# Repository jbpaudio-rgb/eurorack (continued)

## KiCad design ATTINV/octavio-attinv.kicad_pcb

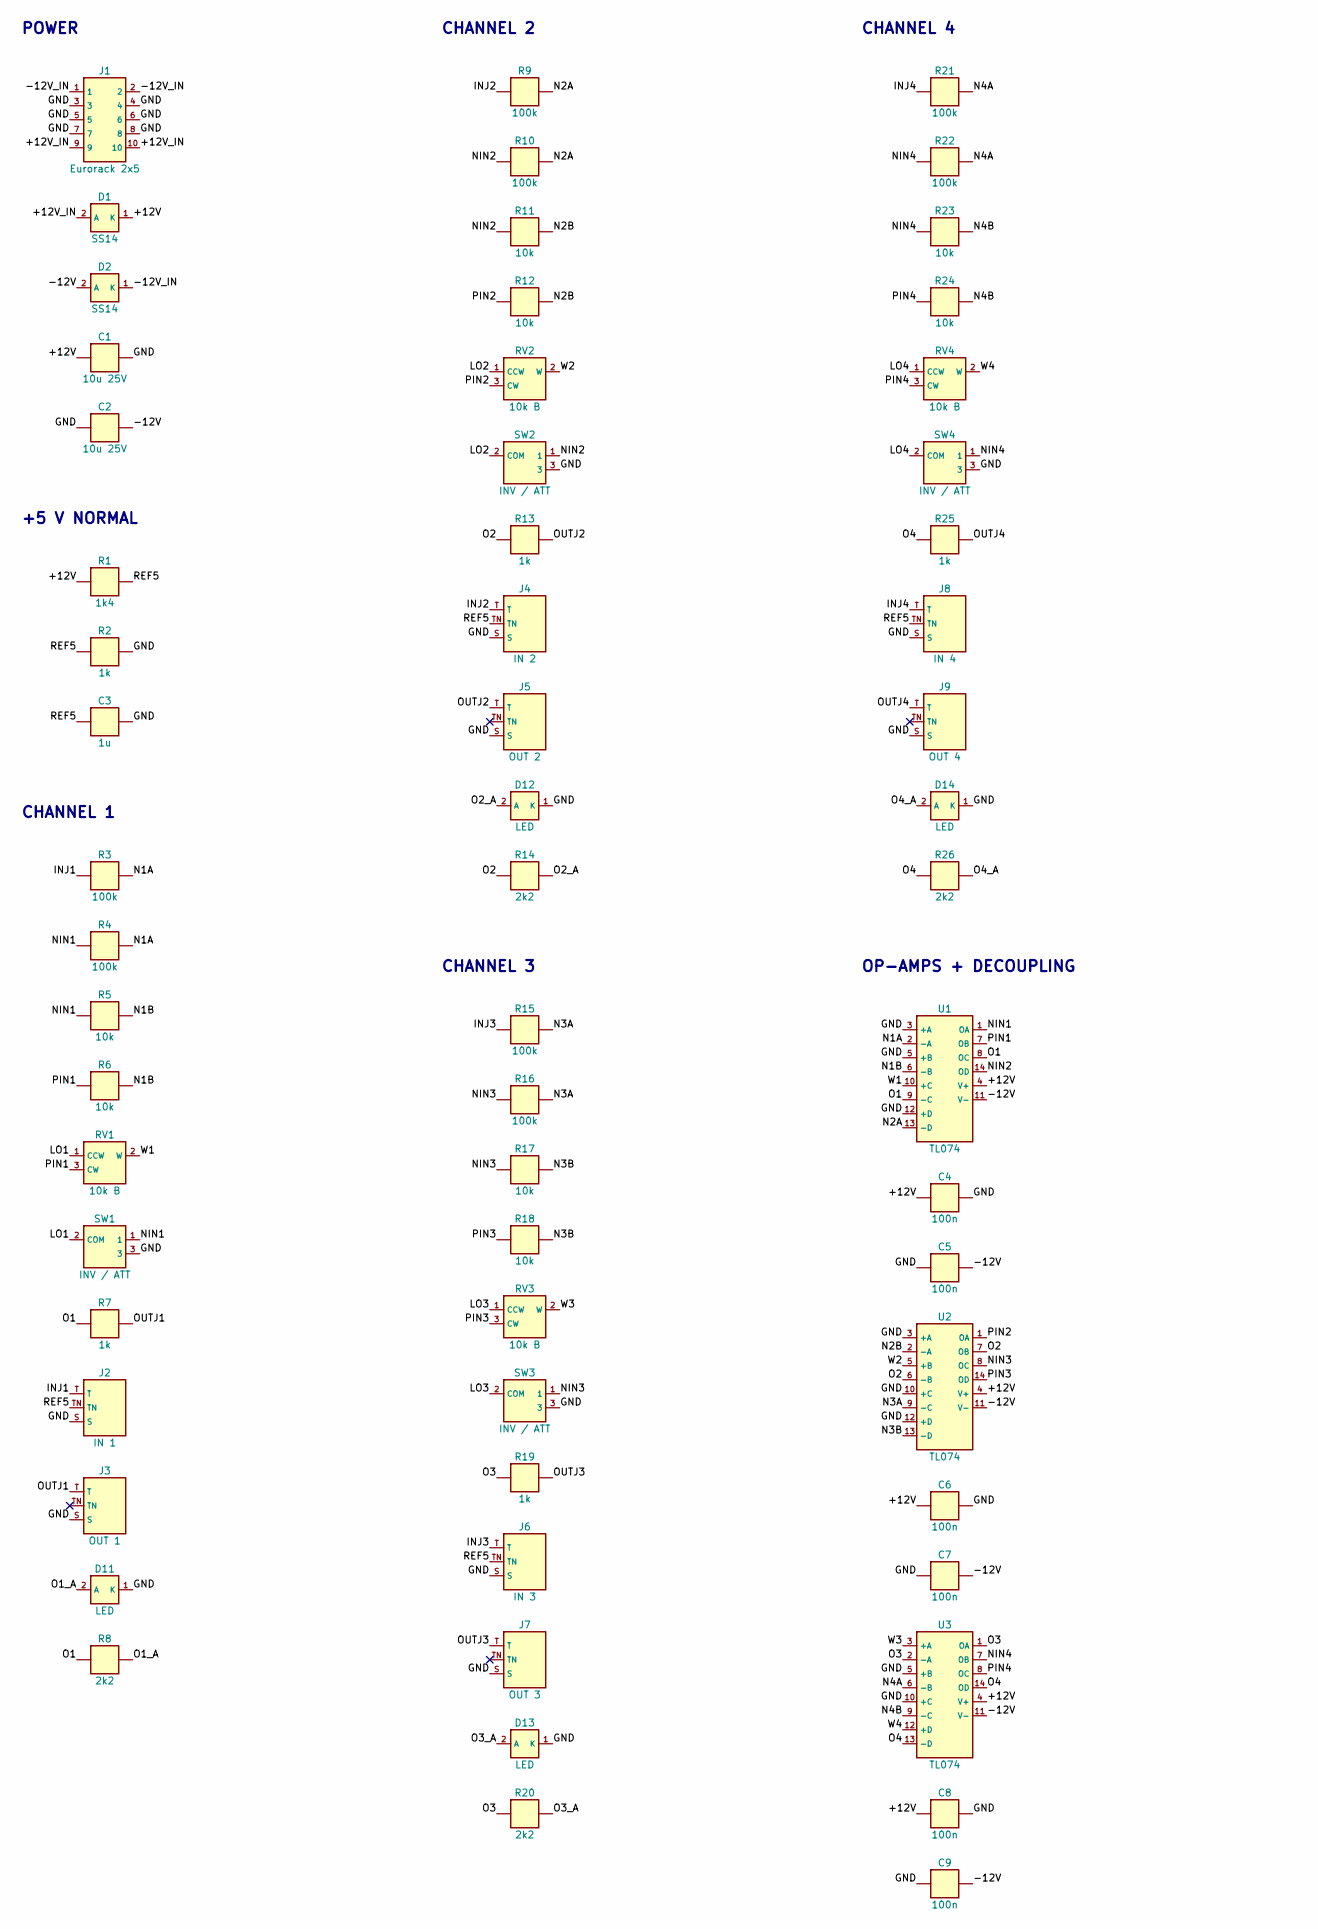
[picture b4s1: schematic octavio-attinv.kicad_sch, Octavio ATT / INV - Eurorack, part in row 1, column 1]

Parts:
C1, C2: 10u 25V; C_1206_3216Metric; MPN X5R/X7R 1206
C3: 1u; C_0603_1608Metric; MPN X7R 0603 25 V
C4, C5, C6, C7, C8, C9: 100n; C_0603_1608Metric
D1, D2: SS14; D_SMA; MPN SS14 (40 V 1 A Schottky)
D11, D12, D13, D14: LED; LED_D3.0mm; MPN LED 3 mm bicolore 2 pattes rouge / vert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
J1: Eurorack 2x5; IDC-Header_2x05_P2.54mm_Vertical; MPN Shrouded header 2x5 2.54 mm
J2: IN 1; Jack_3.5mm_Thonkiconn_PJ398SM; MPN QingPu WQP-PJ301M-12 (Thonkiconn)
J3: OUT 1; Jack_3.5mm_Thonkiconn_PJ398SM; MPN QingPu WQP-PJ301M-12 (Thonkiconn)
J4: IN 2; Jack_3.5mm_Thonkiconn_PJ398SM; MPN QingPu WQP-PJ301M-12 (Thonkiconn)
J5: OUT 2; Jack_3.5mm_Thonkiconn_PJ398SM; MPN QingPu WQP-PJ301M-12 (Thonkiconn)
J6: IN 3; Jack_3.5mm_Thonkiconn_PJ398SM; MPN QingPu WQP-PJ301M-12 (Thonkiconn)
J7: OUT 3; Jack_3.5mm_Thonkiconn_PJ398SM; MPN QingPu WQP-PJ301M-12 (Thonkiconn)
J8: IN 4; Jack_3.5mm_Thonkiconn_PJ398SM; MPN QingPu WQP-PJ301M-12 (Thonkiconn)
J9: OUT 4; Jack_3.5mm_Thonkiconn_PJ398SM; MPN QingPu WQP-PJ301M-12 (Thonkiconn)
R1: 1k4; R_0603_1608Metric
R2, R7, R13, R19, R25: 1k; R_0603_1608Metric
R3, R4, R9, R10, R15, R16, R21, R22: 100k; R_0603_1608Metric
R5, R6, R11, R12, R17, R18, R23, R24: 10k; R_0603_1608Metric
R8, R14, R20, R26: 2k2; R_0603_1608Metric
RV1, RV2, RV3, RV4: 10k B; Pot_Alpha_9mm_Vertical; MPN POT-R09V-10K B (9 mm vertical)
SW1, SW2, SW3, SW4: INV / ATT; Toggle_SPDT_Dailywell_2MS1; MPN Dailywell 2MS1T1B1M2QES (SPDT ON-ON) : 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
U1, U2, U3: TL074; SOIC-14_3.9x8.7mm_P1.27mm; MPN TL074CDR

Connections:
+12V: C1.1, C4.1, C6.1, C8.1, D1.1 (K), R1.1, U1.4 (V+), U2.4 (V+), U3.4 (V+)
+12V_IN: D1.2 (A), J1.9, J1.10
-12V: C2.2, C5.2, C7.2, C9.2, D2.2 (A), U1.11 (V-), U2.11 (V-), U3.11 (V-)
-12V_IN: D2.1 (K), J1.1, J1.2
GND: C1.2, C2.1, C3.2, C4.2, C5.1, C6.2, C7.1, C8.2, C9.1, D11.1 (K), D12.1 (K), D13.1 (K), D14.1 (K), J1.3, J1.4, J1.5, J1.6, J1.7, J1.8, J2.S, J3.S, J4.S, J5.S, J6.S, J7.S, J8.S, J9.S, R2.2, SW1.3, SW2.3, SW3.3, SW4.3, U1.3 (+A), U1.5 (+B), U1.12 (+D), U2.3 (+A), U2.10 (+C), U2.12 (+D), U3.5 (+B), U3.10 (+C)
INJ1: J2.T, R3.1
INJ2: J4.T, R9.1
INJ3: J6.T, R15.1
INJ4: J8.T, R21.1
LO1: RV1.1 (CCW), SW1.2 (COM)
LO2: RV2.1 (CCW), SW2.2 (COM)
LO3: RV3.1 (CCW), SW3.2 (COM)
LO4: RV4.1 (CCW), SW4.2 (COM)
N1A: R3.2, R4.2, U1.2 (-A)
N1B: R5.2, R6.2, U1.6 (-B)
N2A: R9.2, R10.2, U1.13 (-D)
N2B: R11.2, R12.2, U2.2 (-A)
N3A: R15.2, R16.2, U2.9 (-C)
N3B: R17.2, R18.2, U2.13 (-D)
N4A: R21.2, R22.2, U3.6 (-B)
N4B: R23.2, R24.2, U3.9 (-C)
NIN1: R4.1, R5.1, SW1.1, U1.1 (OA)
NIN2: R10.1, R11.1, SW2.1, U1.14 (OD)
NIN3: R16.1, R17.1, SW3.1, U2.8 (OC)
NIN4: R22.1, R23.1, SW4.1, U3.7 (OB)
O1: R7.1, R8.1, U1.8 (OC), U1.9 (-C)
O1_A: D11.2 (A), R8.2
O2: R13.1, R14.1, U2.6 (-B), U2.7 (OB)
O2_A: D12.2 (A), R14.2
O3: R19.1, R20.1, U3.1 (OA), U3.2 (-A)
O3_A: D13.2 (A), R20.2
O4: R25.1, R26.1, U3.13 (-D), U3.14 (OD)
O4_A: D14.2 (A), R26.2
OUTJ1: J3.T, R7.2
OUTJ2: J5.T, R13.2
OUTJ3: J7.T, R19.2
OUTJ4: J9.T, R25.2
PIN1: R6.1, RV1.3 (CW), U1.7 (OB)
PIN2: R12.1, RV2.3 (CW), U2.1 (OA)
PIN3: R18.1, RV3.3 (CW), U2.14 (OD)
PIN4: R24.1, RV4.3 (CW), U3.8 (OC)
REF5: C3.1, J2.TN, J4.TN, J6.TN, J8.TN, R1.2, R2.1
W1: RV1.2 (W), U1.10 (+C)
W2: RV2.2 (W), U2.5 (+B)
W3: RV3.2 (W), U3.3 (+A)
W4: RV4.2 (W), U3.12 (+D)

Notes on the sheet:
POWER
+5 V NORMAL
CHANNEL 1
CHANNEL 2
CHANNEL 3
CHANNEL 4
OP-AMPS + DECOUPLING
NOTES
- Par canal : IN -> inverseur 100k (-IN) -> inverseur 10k (+IN, basse impedance) ; pot 10k B entre +IN et -IN ; curseur -> suiveur -> 1k -> OUT.
- Inverseur INV / ATT : INV = bas du pot sur -IN (attenuverteur -1..+1), ATT = bas du pot a la masse (attenuateur 0..1).
- Entree vide : normalisee sur +5 V (diviseur 14k / 10k sur +12 V) -> le bouton donne un offset de -5 a +5 V.
- LED bicolore 2 pattes : rouge = sortie positive, vert = negative.
- -12V = bande rouge du cable.

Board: 2 copper layers, 61 parts (41 on the bottom side), 46 nets, no tracks yet.

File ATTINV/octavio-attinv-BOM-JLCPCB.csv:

Comment,Designator,Footprint,LCSC Part #,Notes
10u 25V X5R/X7R 1206,"C1,C2",C_1206_3216Metric,,X5R/X7R 1206 - SMT bottom - laisser JLC choisir (Basic de preference)
1u X7R 0603 25 V,C3,C_0603_1608Metric,,X7R 0603 25 V - SMT bottom - laisser JLC choisir (Basic de preference)
100n,"C4,C5,C6,C7,C8,C9",C_0603_1608Metric,,SMT bottom - laisser JLC choisir (Basic de preference)
SS14,"D1,D2",D_SMA,,SS14 (40 V 1 A Schottky) - SMT bottom - laisser JLC choisir (Basic de preference)
LED,"D11,D12,D13,D14",LED_D3.0mm,,"LED 3 mm bicolore 2 pattes rouge / vert (rouge = +, vert = -) - THT (wave soldering) - laisser JLC choisir (Basic de preference)"
Eurorack 2x5,J1,IDC-Header_2x05_P2.54mm_Vertical,,Shrouded header 2x5 2.54 mm - THT (wave soldering) - laisser JLC choisir (Basic de preference)
IN 1,J2,Jack_3.5mm_Thonkiconn_PJ398SM,C9900080080,QingPu WQP-PJ301M-12 (Thonkiconn) - THT (wave soldering)
OUT 1,J3,Jack_3.5mm_Thonkiconn_PJ398SM,C9900080080,QingPu WQP-PJ301M-12 (Thonkiconn) - THT (wave soldering)
IN 2,J4,Jack_3.5mm_Thonkiconn_PJ398SM,C9900080080,QingPu WQP-PJ301M-12 (Thonkiconn) - THT (wave soldering)
OUT 2,J5,Jack_3.5mm_Thonkiconn_PJ398SM,C9900080080,QingPu WQP-PJ301M-12 (Thonkiconn) - THT (wave soldering)
IN 3,J6,Jack_3.5mm_Thonkiconn_PJ398SM,C9900080080,QingPu WQP-PJ301M-12 (Thonkiconn) - THT (wave soldering)
OUT 3,J7,Jack_3.5mm_Thonkiconn_PJ398SM,C9900080080,QingPu WQP-PJ301M-12 (Thonkiconn) - THT (wave soldering)
IN 4,J8,Jack_3.5mm_Thonkiconn_PJ398SM,C9900080080,QingPu WQP-PJ301M-12 (Thonkiconn) - THT (wave soldering)
OUT 4,J9,Jack_3.5mm_Thonkiconn_PJ398SM,C9900080080,QingPu WQP-PJ301M-12 (Thonkiconn) - THT (wave soldering)
14k 1% 0805,R1,R_0603_1608Metric,,SMT bottom - laisser JLC choisir (Basic de preference)
10k 1% 0805,"R2,R5,R6,R11,R12,R17,R18,R23,R24",R_0603_1608Metric,,SMT bottom - laisser JLC choisir (Basic de preference)
100k 1% 0805,"R3,R4,R9,R10,R15,R16,R21,R22",R_0603_1608Metric,,SMT bottom - laisser JLC choisir (Basic de preference)
1k 1% 0805,"R7,R13,R19,R25",R_0603_1608Metric,,SMT bottom - laisser JLC choisir (Basic de preference)
2k2 1% 0805,"R8,R14,R20,R26",R_0603_1608Metric,,SMT bottom - laisser JLC choisir (Basic de preference)
10k B,"RV1,RV2,RV3,RV4",Pot_Alpha_9mm_Vertical,,POT-R09V-10K B (9 mm vertical) - THT (wave soldering) - laisser JLC choisir (Basic de preference)
INV / ATT,"SW1,SW2,SW3,SW4",Toggle_SPDT_Dailywell_2MS1,,"Dailywell 2MS1T1B1M2QES (SPDT ON-ON) : levier à gauche = INV, à droite = ATT - THT (wave soldering) - laisser JLC choisir (Basic de preference)"
TL074CDR,"U1,U2,U3",SOIC-14_3.9x8.7mm_P1.27mm,C12594,TL074CDR - SMT bottom

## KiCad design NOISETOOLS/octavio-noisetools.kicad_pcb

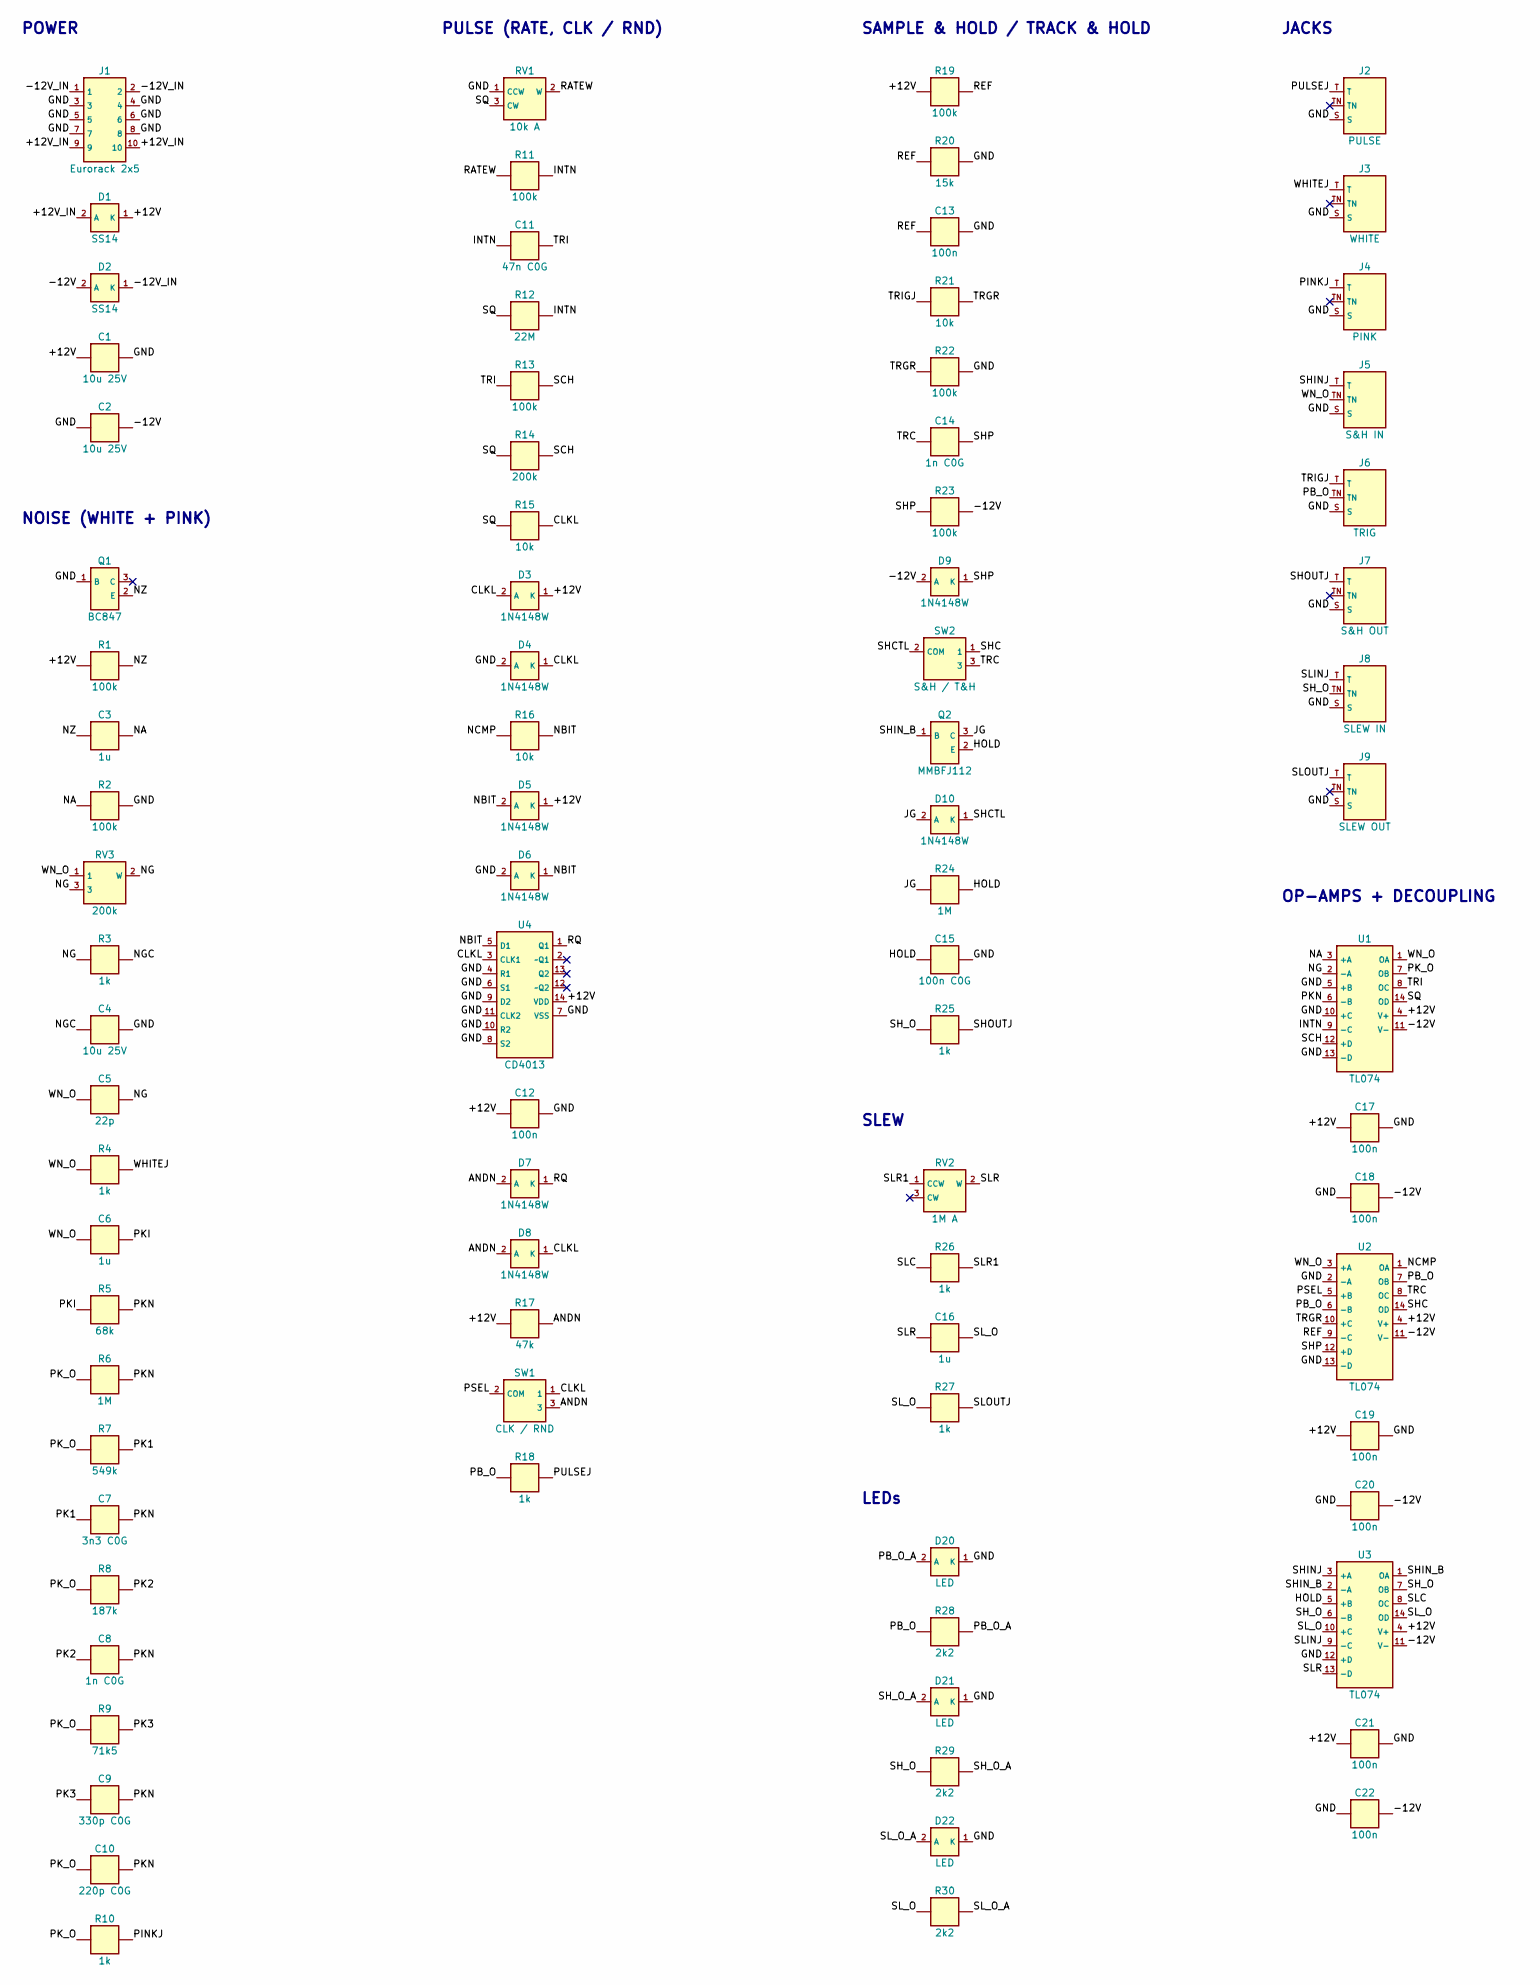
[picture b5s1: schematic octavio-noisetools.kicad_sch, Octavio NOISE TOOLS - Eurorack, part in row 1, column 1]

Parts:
C1, C2, C4: 10u 25V; C_1206_3216Metric; MPN X5R/X7R 1206
C3, C6: 1u; C_0603_1608Metric; MPN X7R 0603 25 V
C5: 22p; C_0603_1608Metric
C7: 3n3 C0G; C_0603_1608Metric; MPN C0G/NP0 0603
C8, C14: 1n C0G; C_0603_1608Metric; MPN C0G/NP0 0603
C9: 330p C0G; C_0603_1608Metric; MPN C0G/NP0 0603
C10: 220p C0G; C_0603_1608Metric; MPN C0G/NP0 0603
C11: 47n C0G; C_0805_2012Metric; MPN C0G/NP0 0805
C12, C13, C17, C18, C19, C20, C21, C22: 100n; C_0603_1608Metric
C15: 100n C0G; C_1206_3216Metric; MPN C0G/NP0 1206 (condensateur de maintien,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
C16: 1u; C_1206_3216Metric; MPN X7R 1206 25 V
D1, D2: SS14; D_SMA; MPN SS14 (40 V 1 A Schottky)
D3, D4, D5, D6, D7, D8, D9, D10: 1N4148W; D_SOD-123; MPN 1N4148W
D20: LED; LED_D3.0mm; MPN LED 3 mm ambre (PULSE)
D21: LED; LED_D3.0mm; MPN LED 3 mm rouge (S&H, positif)
D22: LED; LED_D3.0mm; MPN LED 3 mm rouge (SLEW, positif)
J1: Eurorack 2x5; IDC-Header_2x05_P2.54mm_Vertical; MPN Shrouded header 2x5 2.54 mm
J2: PULSE; Jack_3.5mm_Thonkiconn_PJ398SM; MPN QingPu WQP-PJ301M-12 (Thonkiconn)
J3: WHITE; Jack_3.5mm_Thonkiconn_PJ398SM; MPN QingPu WQP-PJ301M-12 (Thonkiconn)
J4: PINK; Jack_3.5mm_Thonkiconn_PJ398SM; MPN QingPu WQP-PJ301M-12 (Thonkiconn)
J5: S&H IN; Jack_3.5mm_Thonkiconn_PJ398SM; MPN QingPu WQP-PJ301M-12 (Thonkiconn)
J6: TRIG; Jack_3.5mm_Thonkiconn_PJ398SM; MPN QingPu WQP-PJ301M-12 (Thonkiconn)
J7: S&H OUT; Jack_3.5mm_Thonkiconn_PJ398SM; MPN QingPu WQP-PJ301M-12 (Thonkiconn)
J8: SLEW IN; Jack_3.5mm_Thonkiconn_PJ398SM; MPN QingPu WQP-PJ301M-12 (Thonkiconn)
J9: SLEW OUT; Jack_3.5mm_Thonkiconn_PJ398SM; MPN QingPu WQP-PJ301M-12 (Thonkiconn)
Q1: BC847; SOT-23; MPN BC847C (jonction base-émetteur en avala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
Q2: MMBFJ112; SOT-23; MPN MMBFJ112 (JFET N, D-S-G)
R1, R2, R11, R13, R19, R22, R23: 100k; R_0603_1608Metric
R3, R4, R10, R18, R25, R26, R27: 1k; R_0603_1608Metric
R5: 68k; R_0603_1608Metric
R6, R24: 1M; R_0603_1608Metric
R7: 549k; R_0603_1608Metric
R8: 187k; R_0603_1608Metric
R9: 71k5; R_0603_1608Metric
R12: 22M; R_0603_1608Metric
R14: 200k; R_0603_1608Metric
R15, R16, R21: 10k; R_0603_1608Metric
R17: 47k; R_0603_1608Metric
R20: 15k; R_0603_1608Metric
R28, R29, R30: 2k2; R_0603_1608Metric
RV1: 10k A; Pot_Alpha_9mm_Vertical; MPN POT-R09V-10K A (9 mm vertical, log)
RV2: 1M A; Pot_Alpha_9mm_Vertical; MPN POT-R09V-1M A (9 mm vertical, log)
RV3: 200k; Trim_SMD_Bourns_3314J; MPN Bourns 3314J-1-204E (niveau du bruit : 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
SW1: CLK / RND; Toggle_SPDT_Dailywell_2MS1; MPN Dailywell 2MS1T1B1M2QES (SPDT ON-ON)
SW2: S&H / T&H; Toggle_SPDT_Dailywell_2MS1; MPN Dailywell 2MS1T1B1M2QES (SPDT ON-ON)
U1, U2, U3: TL074; SOIC-14_3.9x8.7mm_P1.27mm; MPN TL074CDR
U4: CD4013; SOIC-14_3.9x8.7mm_P1.27mm; MPN CD4013BM96

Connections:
+12V: C1.1, C12.1, C17.1, C19.1, C21.1, D1.1 (K), D3.1 (K), D5.1 (K), R1.1, R17.1, R19.1, U1.4 (V+), U2.4 (V+), U3.4 (V+), U4.14 (VDD)
+12V_IN: D1.2 (A), J1.9, J1.10
-12V: C2.2, C18.2, C20.2, C22.2, D2.2 (A), D9.2 (A), R23.2, U1.11 (V-), U2.11 (V-), U3.11 (V-)
-12V_IN: D2.1 (K), J1.1, J1.2
ANDN: D7.2 (A), D8.2 (A), R17.2, SW1.3
CLKL: D3.2 (A), D4.1 (K), D8.1 (K), R15.2, SW1.1, U4.3 (CLK1)
GND: C1.2, C2.1, C4.2, C12.2, C13.2, C15.2, C17.2, C18.1, C19.2, C20.1, C21.2, C22.1, D4.2 (A), D6.2 (A), D20.1 (K), D21.1 (K), D22.1 (K), J1.3, J1.4, J1.5, J1.6, J1.7, J1.8, J2.S, J3.S, J4.S, J5.S, J6.S, J7.S, J8.S, J9.S, Q1.1 (B), R2.2, R20.2, R22.2, RV1.1 (CCW), U1.5 (+B), U1.10 (+C), U1.13 (-D), U2.2 (-A), U2.13 (-D), U3.12 (+D), U4.4 (R1), U4.6 (S1), U4.7 (VSS), U4.8 (S2), U4.9 (D2), U4.10 (R2), U4.11 (CLK2)
INTN: C11.1, R11.2, R12.2, U1.9 (-C)
JG: D10.2 (A), Q2.3 (C), R24.1
NA: C3.2, R2.1, U1.3 (+A)
NBIT: D5.2 (A), D6.1 (K), R16.2, U4.5 (D1)
NCMP: R16.1, U2.1 (OA)
NG: C5.2, R3.1, RV3.2 (W), RV3.3, U1.2 (-A)
NGC: C4.1, R3.2
NZ: C3.1, Q1.2 (E), R1.2
PB_O: J6.TN, R18.1, R28.1, U2.6 (-B), U2.7 (OB)
PB_O_A: D20.2 (A), R28.2
PINKJ: J4.T, R10.2
PK1: C7.1, R7.2
PK2: C8.1, R8.2
PK3: C9.1, R9.2
PKI: C6.2, R5.1
PKN: C7.2, C8.2, C9.2, C10.2, R5.2, R6.2, U1.6 (-B)
PK_O: C10.1, R6.1, R7.1, R8.1, R9.1, R10.1, U1.7 (OB)
PSEL: SW1.2 (COM), U2.5 (+B)
PULSEJ: J2.T, R18.2
RATEW: R11.1, RV1.2 (W)
REF: C13.1, R19.2, R20.1, U2.9 (-C)
RQ: D7.1 (K), U4.1 (Q1)
SCH: R13.2, R14.2, U1.12 (+D)
SHC: SW2.1, U2.14 (OD)
SHCTL: D10.1 (K), SW2.2 (COM)
SHINJ: J5.T, U3.3 (+A)
SHOUTJ: J7.T, R25.2
SHP: C14.2, D9.1 (K), R23.1, U2.12 (+D)
SH_O: J8.TN, R25.1, R29.1, U3.6 (-B), U3.7 (OB)
SH_O_A: D21.2 (A), R29.2
SLC: R26.1, U3.8 (OC)
SLINJ: J8.T, U3.9 (-C)
SLOUTJ: J9.T, R27.2
SLR: C16.1, RV2.2 (W), U3.13 (-D)
SLR1: R26.2, RV2.1 (CCW)
SL_O: C16.2, R27.1, R30.1, U3.10 (+C), U3.14 (OD)
SL_O_A: D22.2 (A), R30.2
SQ: R12.1, R14.1, R15.1, RV1.3 (CW), U1.14 (OD)
TRC: C14.1, SW2.3, U2.8 (OC)
TRGR: R21.2, R22.1, U2.10 (+C)
TRI: C11.2, R13.1, U1.8 (OC)
TRIGJ: J6.T, R21.1
WHITEJ: J3.T, R4.2
WN_O: C5.1, C6.1, J5.TN, R4.1, RV3.1, U1.1 (OA), U2.3 (+A)

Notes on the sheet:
POWER
NOISE (WHITE + PINK)
PULSE (RATE, CLK / RND)
SAMPLE & HOLD / TRACK & HOLD
SLEW
LEDs
JACKS
OP-AMPS + DECOUPLING
NOTES
- Bruit : jonction base-emetteur d'un BC847 en avalanche, ampli x1..x200 (RV3 : regler 10 V crete a crete sur WHITE).
- PINK : filtre -3 dB/octave (4 branches RC dans la contre-reaction), +/-0,3 dB de 20 Hz a 20 kHz.
- PULSE : integrateur + Schmitt, vitesse = pot A10k sur le carre (0,5 a 106 Hz). RND : CD4013 echantillonne le bruit a chaque front, ET avec l'horloge.
- S&H / T&H : JFET MMBFJ112 + 100n C0G + tampon TL074. S&H : impulsion de 70 us sur front montant ; T&H : suit tant que TRIG est haut.
- Normalisations : S&H IN <- WHITE, TRIG <- PULSE, SLEW IN <- S&H OUT.
- -12V = bande rouge du cable.

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
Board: 2 copper layers, 85 parts (70 on the bottom side), 53 nets, no tracks yet.

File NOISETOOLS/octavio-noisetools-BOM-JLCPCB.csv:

Comment,Designator,Footprint,LCSC Part #,Notes
10u 25V X5R/X7R 1206,"C1,C2,C4",C_1206_3216Metric,,X5R/X7R 1206 - SMT bottom - laisser JLC choisir (Basic de preference)
220p C0G C0G/NP0 0603,C10,C_0603_1608Metric,,C0G/NP0 0603 - SMT bottom - laisser JLC choisir (Basic de preference)
47n C0G C0G/NP0 0805,C11,C_0805_2012Metric,,C0G/NP0 0805 - SMT bottom - laisser JLC choisir (Basic de preference)
100n,"C12,C13,C17,C18,C19,C20,C21,C22",C_0603_1608Metric,,SMT bottom - laisser JLC choisir (Basic de preference)
100n C0G C0G/NP0 1206,C15,C_1206_3216Metric,,"C0G/NP0 1206 (condensateur de maintien, très faible fuite) - SMT bottom - laisser JLC choisir (Basic de preference)"
1u X7R 1206 25 V,C16,C_1206_3216Metric,,X7R 1206 25 V - SMT bottom - laisser JLC choisir (Basic de preference)
1u X7R 0603 25 V,"C3,C6",C_0603_1608Metric,,X7R 0603 25 V - SMT bottom - laisser JLC choisir (Basic de preference)
22p,C5,C_0603_1608Metric,,SMT bottom - laisser JLC choisir (Basic de preference)
3n3 C0G C0G/NP0 0603,C7,C_0603_1608Metric,,C0G/NP0 0603 - SMT bottom - laisser JLC choisir (Basic de preference)
1n C0G C0G/NP0 0603,"C8,C14",C_0603_1608Metric,,C0G/NP0 0603 - SMT bottom - laisser JLC choisir (Basic de preference)
330p C0G C0G/NP0 0603,C9,C_0603_1608Metric,,C0G/NP0 0603 - SMT bottom - laisser JLC choisir (Basic de preference)
SS14,"D1,D2",D_SMA,,SS14 (40 V 1 A Schottky) - SMT bottom - laisser JLC choisir (Basic de preference)
LED,D20,LED_D3.0mm,,LED 3 mm ambre (PULSE) - THT (wave soldering) - laisser JLC choisir (Basic de preference)
LED,D21,LED_D3.0mm,,"LED 3 mm rouge (S&H, positif) - THT (wave soldering) - laisser JLC choisir (Basic de preference)"
LED,D22,LED_D3.0mm,,"LED 3 mm rouge (SLEW, positif) - THT (wave soldering) - laisser JLC choisir (Basic de preference)"
1N4148W,"D3,D4,D5,D6,D7,D8,D9,D10",D_SOD-123,,1N4148W - SMT bottom - laisser JLC choisir (Basic de preference)
Eurorack 2x5,J1,IDC-Header_2x05_P2.54mm_Vertical,,Shrouded header 2x5 2.54 mm - THT (wave soldering) - laisser JLC choisir (Basic de preference)
PULSE,J2,Jack_3.5mm_Thonkiconn_PJ398SM,C9900080080,QingPu WQP-PJ301M-12 (Thonkiconn) - THT (wave soldering)
WHITE,J3,Jack_3.5mm_Thonkiconn_PJ398SM,C9900080080,QingPu WQP-PJ301M-12 (Thonkiconn) - THT (wave soldering)
PINK,J4,Jack_3.5mm_Thonkiconn_PJ398SM,C9900080080,QingPu WQP-PJ301M-12 (Thonkiconn) - THT (wave soldering)
S&H IN,J5,Jack_3.5mm_Thonkiconn_PJ398SM,C9900080080,QingPu WQP-PJ301M-12 (Thonkiconn) - THT (wave soldering)
TRIG,J6,Jack_3.5mm_Thonkiconn_PJ398SM,C9900080080,QingPu WQP-PJ301M-12 (Thonkiconn) - THT (wave soldering)
S&H OUT,J7,Jack_3.5mm_Thonkiconn_PJ398SM,C9900080080,QingPu WQP-PJ301M-12 (Thonkiconn) - THT (wave soldering)
SLEW IN,J8,Jack_3.5mm_Thonkiconn_PJ398SM,C9900080080,QingPu WQP-PJ301M-12 (Thonkiconn) - THT (wave soldering)
SLEW OUT,J9,Jack_3.5mm_Thonkiconn_PJ398SM,C9900080080,QingPu WQP-PJ301M-12 (Thonkiconn) - THT (wave soldering)
BC847C,Q1,SOT-23,,BC847C (jonction base-émetteur en avalanche = source de bruit) - SMT bottom - laisser JLC choisir (Basic de preference)
MMBFJ112,Q2,SOT-23,,"MMBFJ112 (JFET N, D-S-G) - SMT bottom - laisser JLC choisir (Basic de preference)"
100k 1% 0805,"R1,R2,R11,R13,R19,R22,R23,R24",R_0603_1608Metric,,SMT bottom - laisser JLC choisir (Basic de preference)
22M 1% 0805,R12,R_0603_1608Metric,,SMT bottom - laisser JLC choisir (Basic de preference)
200k 1% 0805,R14,R_0603_1608Metric,,SMT bottom - laisser JLC choisir (Basic de preference)
10k 1% 0805,"R15,R16,R21",R_0603_1608Metric,,SMT bottom - laisser JLC choisir (Basic de preference)
47k 1% 0805,R17,R_0603_1608Metric,,SMT bottom - laisser JLC choisir (Basic de preference)
15k 1% 0805,R20,R_0603_1608Metric,,SMT bottom - laisser JLC choisir (Basic de preference)
2k2 1% 0805,"R28,R29,R30",R_0603_1608Metric,,SMT bottom - laisser JLC choisir (Basic de preference)
1k 1% 0805,"R3,R4,R10,R18,R25,R26,R27",R_0603_1608Metric,,SMT bottom - laisser JLC choisir (Basic de preference)
68k 1% 0805,R5,R_0603_1608Metric,,SMT bottom - laisser JLC choisir (Basic de preference)
1M 1% 0805,R6,R_0603_1608Metric,,SMT bottom - laisser JLC choisir (Basic de preference)
549k 1% 0805,R7,R_0603_1608Metric,,SMT bottom - laisser JLC choisir (Basic de preference)
187k 1% 0805,R8,R_0603_1608Metric,,SMT bottom - laisser JLC choisir (Basic de preference)
71k5 1% 0805,R9,R_0603_1608Metric,,SMT bottom - laisser JLC choisir (Basic de preference)
10k A,RV1,Pot_Alpha_9mm_Vertical,,"POT-R09V-10K A (9 mm vertical, log) - THT (wave soldering) - laisser JLC choisir (Basic de preference)"
1M A,RV2,Pot_Alpha_9mm_Vertical,,"POT-R09V-1M A (9 mm vertical, log) - THT (wave soldering) - laisser JLC choisir (Basic de preference)"
200k Bourns 3314J-1-204E,RV3,Trim_SMD_Bourns_3314J,,Bourns 3314J-1-204E (niveau du bruit : 10 V crête à crête) - SMT bottom - laisser JLC choisir (Basic de preference)
CLK / RND,SW1,Toggle_SPDT_Dailywell_2MS1,,Dailywell 2MS1T1B1M2QES (SPDT ON-ON) - THT (wave soldering) - laisser JLC choisir (Basic de preference)
S&H / T&H,SW2,Toggle_SPDT_Dailywell_2MS1,,Dailywell 2MS1T1B1M2QES (SPDT ON-ON) - THT (wave soldering) - laisser JLC choisir (Basic de preference)
TL074CDR,"U1,U2,U3",SOIC-14_3.9x8.7mm_P1.27mm,C12594,TL074CDR - SMT bottom
CD4013BM96,U4,SOIC-14_3.9x8.7mm_P1.27mm,,CD4013BM96 - SMT bottom - laisser JLC choisir (Basic de preference)

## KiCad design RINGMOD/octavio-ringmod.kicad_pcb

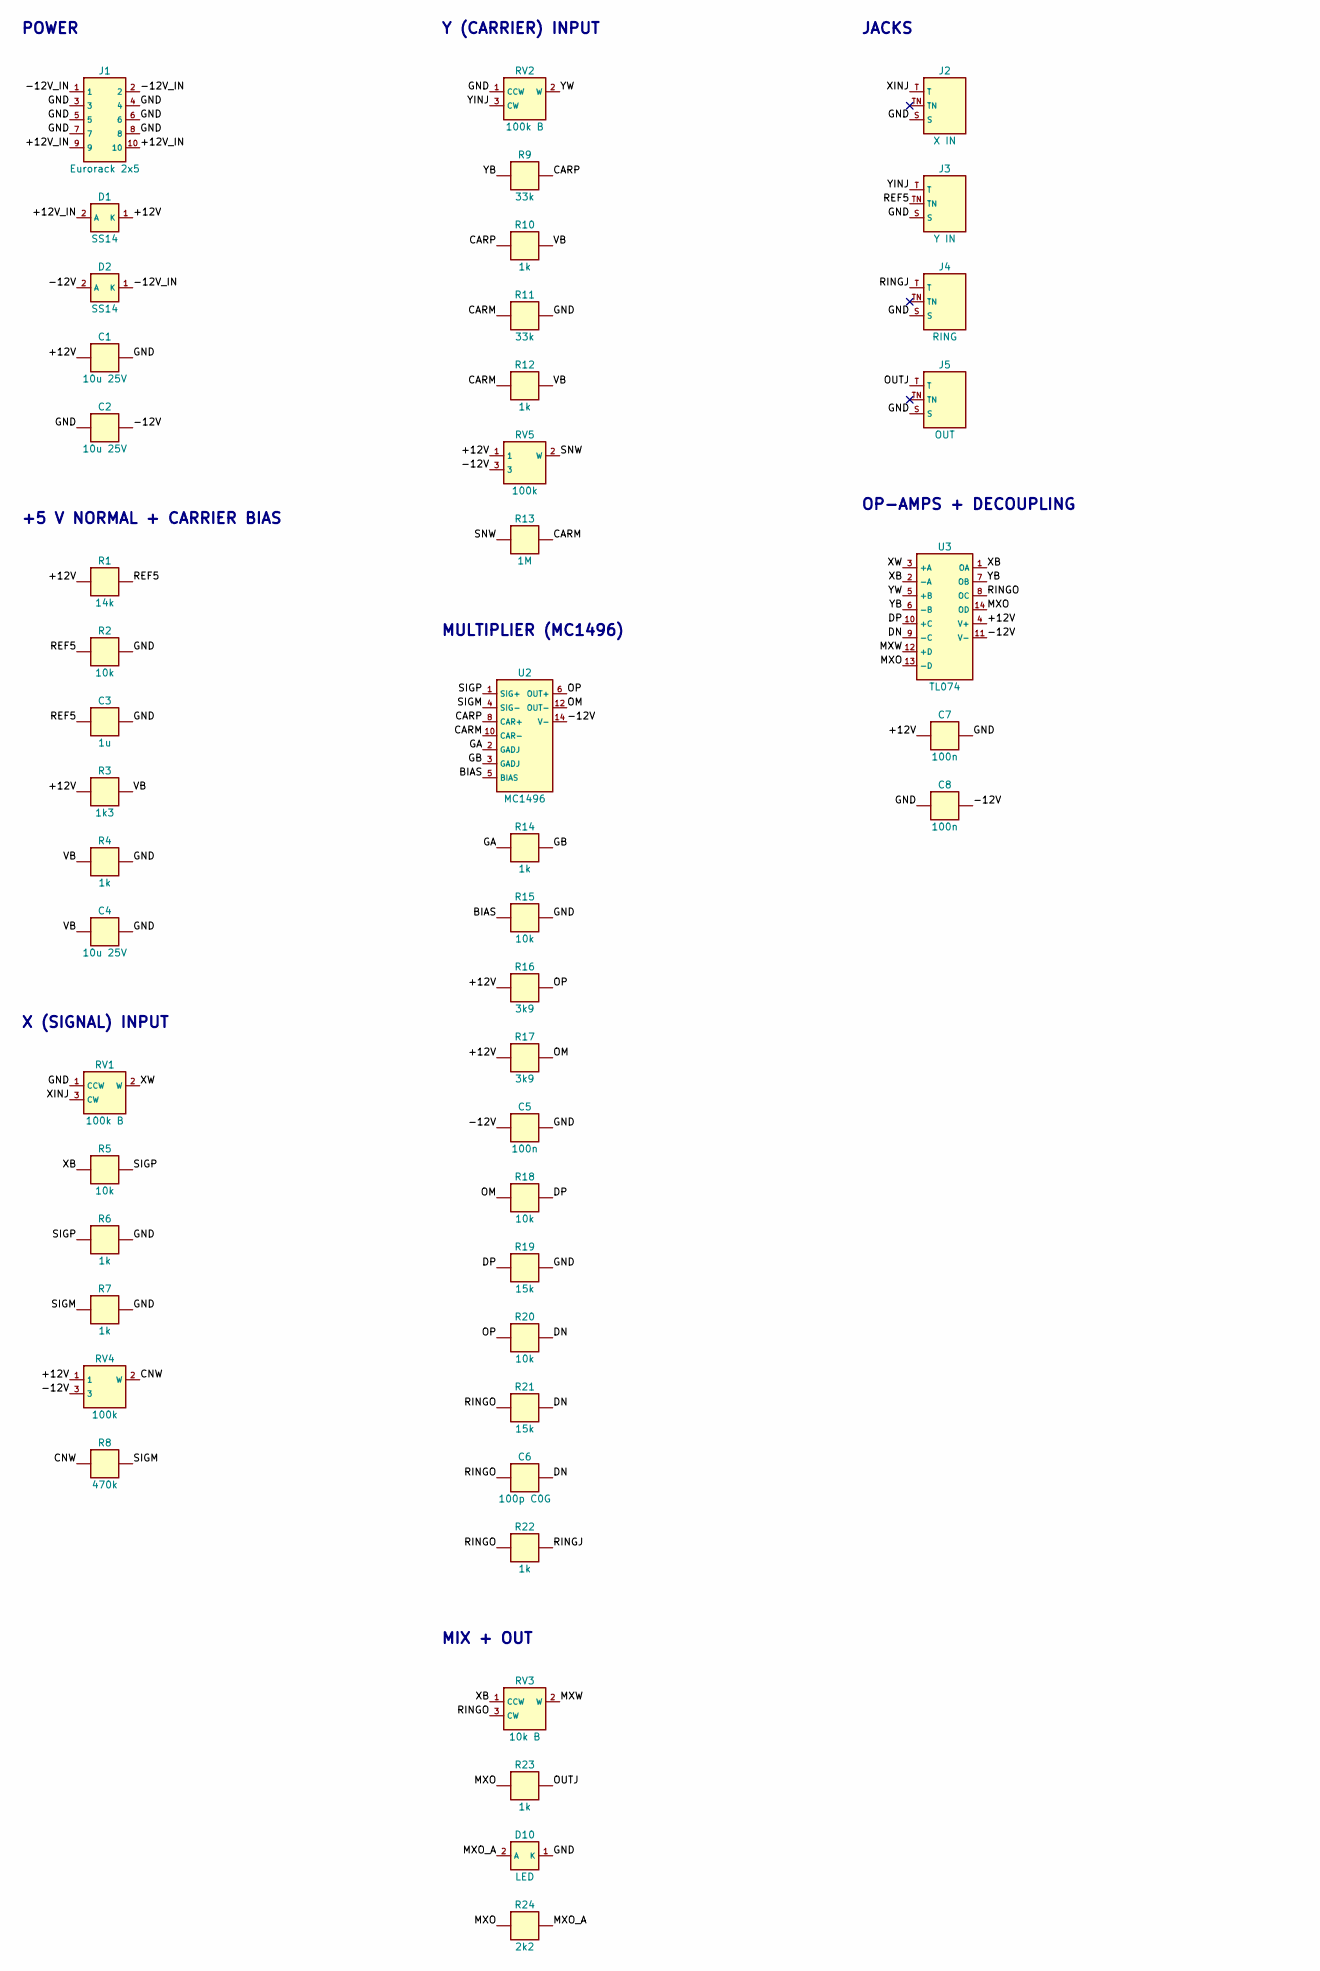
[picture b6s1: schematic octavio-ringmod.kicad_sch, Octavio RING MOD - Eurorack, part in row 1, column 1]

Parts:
C1, C2, C4: 10u 25V; C_1206_3216Metric; MPN X5R/X7R 1206
C3: 1u; C_0603_1608Metric; MPN X7R 0603 25 V
C5, C7, C8: 100n; C_0603_1608Metric
C6: 100p C0G; C_0603_1608Metric; MPN C0G/NP0 0603
D1, D2: SS14; D_SMA; MPN SS14 (40 V 1 A Schottky)
D10: LED; LED_D3.0mm; MPN LED 3 mm bicolore 2 pattes rouge / vert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
J1: Eurorack 2x5; IDC-Header_2x05_P2.54mm_Vertical; MPN Shrouded header 2x5 2.54 mm
J2: X IN; Jack_3.5mm_Thonkiconn_PJ398SM; MPN QingPu WQP-PJ301M-12 (Thonkiconn)
J3: Y IN; Jack_3.5mm_Thonkiconn_PJ398SM; MPN QingPu WQP-PJ301M-12 (Thonkiconn)
J4: RING; Jack_3.5mm_Thonkiconn_PJ398SM; MPN QingPu WQP-PJ301M-12 (Thonkiconn)
J5: OUT; Jack_3.5mm_Thonkiconn_PJ398SM; MPN QingPu WQP-PJ301M-12 (Thonkiconn)
R1: 14k; R_0603_1608Metric
R2, R5, R15, R18, R20: 10k; R_0603_1608Metric
R3: 1k3; R_0603_1608Metric
R4, R6, R7, R10, R12, R14, R22, R23: 1k; R_0603_1608Metric
R8: 470k; R_0603_1608Metric
R9, R11: 33k; R_0603_1608Metric
R13: 1M; R_0603_1608Metric
R16, R17: 3k9; R_0603_1608Metric
R19, R21: 15k; R_0603_1608Metric
R24: 2k2; R_0603_1608Metric
RV1, RV2: 100k B; Pot_Alpha_9mm_Vertical; MPN POT-R09V-100K (9 mm vertical, B100k)
RV3: 10k B; Pot_Alpha_9mm_Vertical; MPN POT-R09V-10K B (9 mm vertical)
RV4: 100k; Trim_SMD_Bourns_3314J; MPN Bourns 3314J-1-104E (CARRIER NULL : Y p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
RV5: 100k; Trim_SMD_Bourns_3314J; MPN Bourns 3314J-1-104E (SIGNAL NULL : X pa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
U2: MC1496; SOIC-14_3.9x8.7mm_P1.27mm; MPN MC1496DR2G (onsemi, SOIC-14)
U3: TL074; SOIC-14_3.9x8.7mm_P1.27mm; MPN TL074CDR

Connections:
+12V: C1.1, C7.1, D1.1 (K), R1.1, R3.1, R16.1, R17.1, RV4.1, RV5.1, U3.4 (V+)
+12V_IN: D1.2 (A), J1.9, J1.10
-12V: C2.2, C5.1, C8.2, D2.2 (A), RV4.3, RV5.3, U2.14 (V-), U3.11 (V-)
-12V_IN: D2.1 (K), J1.1, J1.2
BIAS: R15.1, U2.5 (BIAS)
CARM: R11.1, R12.1, R13.2, U2.10 (CAR-)
CARP: R9.2, R10.1, U2.8 (CAR+)
CNW: R8.1, RV4.2 (W)
DN: C6.2, R20.2, R21.2, U3.9 (-C)
DP: R18.2, R19.1, U3.10 (+C)
GA: R14.1, U2.2 (GADJ)
GB: R14.2, U2.3 (GADJ)
GND: C1.2, C2.1, C3.2, C4.2, C5.2, C7.2, C8.1, D10.1 (K), J1.3, J1.4, J1.5, J1.6, J1.7, J1.8, J2.S, J3.S, J4.S, J5.S, R2.2, R4.2, R6.2, R7.2, R11.2, R15.2, R19.2, RV1.1 (CCW), RV2.1 (CCW)
MXO: R23.1, R24.1, U3.13 (-D), U3.14 (OD)
MXO_A: D10.2 (A), R24.2
MXW: RV3.2 (W), U3.12 (+D)
OM: R17.2, R18.1, U2.12 (OUT-)
OP: R16.2, R20.1, U2.6 (OUT+)
OUTJ: J5.T, R23.2
REF5: C3.1, J3.TN, R1.2, R2.1
RINGJ: J4.T, R22.2
RINGO: C6.1, R21.1, R22.1, RV3.3 (CW), U3.8 (OC)
SIGM: R7.1, R8.2, U2.4 (SIG-)
SIGP: R5.2, R6.1, U2.1 (SIG+)
SNW: R13.1, RV5.2 (W)
VB: C4.1, R3.2, R4.1, R10.2, R12.2
XB: R5.1, RV3.1 (CCW), U3.1 (OA), U3.2 (-A)
XINJ: J2.T, RV1.3 (CW)
XW: RV1.2 (W), U3.3 (+A)
YB: R9.1, U3.6 (-B), U3.7 (OB)
YINJ: J3.T, RV2.3 (CW)
YW: RV2.2 (W), U3.5 (+B)

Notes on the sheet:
POWER
+5 V NORMAL + CARRIER BIAS
X (SIGNAL) INPUT
Y (CARRIER) INPUT
MULTIPLIER (MC1496)
MIX + OUT
JACKS
OP-AMPS + DECOUPLING
NOTES
- Multiplicateur MC1496 : paire basse = X (gain 1k entre 2 et 3), paire haute = Y (porteuse) polarisee a +5,2 V, courant 1 mA (10k sur la broche 5).
- Y LEVEL bas : multiplication propre ; Y LEVEL haut : la paire haute commute (son plus dur, facon modulateur a diodes).
- Y IN vide = +5 V : le module devient un ampli / VCA pour X (Y LEVEL = gain).
- Reglage : RV4 CARRIER NULL (Y seul, X a zero -> minimum en sortie), RV5 SIGNAL NULL (X seul, Y debranche et Y LEVEL a zero -> minimum).
- MIX : fondu sec (X) -> produit ; RING = produit seul ; LED bicolore sur OUT.
- -12V = bande rouge du cable.

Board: 2 copper layers, 47 parts (39 on the bottom side), 32 nets, no tracks yet.

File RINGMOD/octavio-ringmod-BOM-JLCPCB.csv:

Comment,Designator,Footprint,LCSC Part #,Notes
10u 25V X5R/X7R 1206,"C1,C2,C4",C_1206_3216Metric,,X5R/X7R 1206 - SMT bottom - laisser JLC choisir (Basic de preference)
1u X7R 0603 25 V,C3,C_0603_1608Metric,,X7R 0603 25 V - SMT bottom - laisser JLC choisir (Basic de preference)
100n,"C5,C7,C8",C_0603_1608Metric,,SMT bottom - laisser JLC choisir (Basic de preference)
100p C0G C0G/NP0 0603,C6,C_0603_1608Metric,,C0G/NP0 0603 - SMT bottom - laisser JLC choisir (Basic de preference)
SS14,"D1,D2",D_SMA,,SS14 (40 V 1 A Schottky) - SMT bottom - laisser JLC choisir (Basic de preference)
LED,D10,LED_D3.0mm,,"LED 3 mm bicolore 2 pattes rouge / vert (rouge = +, vert = -) - THT (wave soldering) - laisser JLC choisir (Basic de preference)"
Eurorack 2x5,J1,IDC-Header_2x05_P2.54mm_Vertical,,Shrouded header 2x5 2.54 mm - THT (wave soldering) - laisser JLC choisir (Basic de preference)
X IN,J2,Jack_3.5mm_Thonkiconn_PJ398SM,C9900080080,QingPu WQP-PJ301M-12 (Thonkiconn) - THT (wave soldering)
Y IN,J3,Jack_3.5mm_Thonkiconn_PJ398SM,C9900080080,QingPu WQP-PJ301M-12 (Thonkiconn) - THT (wave soldering)
RING,J4,Jack_3.5mm_Thonkiconn_PJ398SM,C9900080080,QingPu WQP-PJ301M-12 (Thonkiconn) - THT (wave soldering)
OUT,J5,Jack_3.5mm_Thonkiconn_PJ398SM,C9900080080,QingPu WQP-PJ301M-12 (Thonkiconn) - THT (wave soldering)
14k 1% 0805,R1,R_0603_1608Metric,,SMT bottom - laisser JLC choisir (Basic de preference)
1M 1% 0805,R13,R_0603_1608Metric,,SMT bottom - laisser JLC choisir (Basic de preference)
3k9 1% 0805,"R16,R17",R_0603_1608Metric,,SMT bottom - laisser JLC choisir (Basic de preference)
15k 1% 0805,"R19,R21",R_0603_1608Metric,,SMT bottom - laisser JLC choisir (Basic de preference)
10k 1% 0805,"R2,R5,R15,R18,R20",R_0603_1608Metric,,SMT bottom - laisser JLC choisir (Basic de preference)
2k2 1% 0805,R24,R_0603_1608Metric,,SMT bottom - laisser JLC choisir (Basic de preference)
1k3 1% 0805,R3,R_0603_1608Metric,,SMT bottom - laisser JLC choisir (Basic de preference)
1k 1% 0805,"R4,R6,R7,R10,R12,R14,R22,R23",R_0603_1608Metric,,SMT bottom - laisser JLC choisir (Basic de preference)
470k 1% 0805,R8,R_0603_1608Metric,,SMT bottom - laisser JLC choisir (Basic de preference)
33k 1% 0805,"R9,R11",R_0603_1608Metric,,SMT bottom - laisser JLC choisir (Basic de preference)
100k B,"RV1,RV2",Pot_Alpha_9mm_Vertical,C9900018037,"POT-R09V-100K (9 mm vertical, B100k) - THT (wave soldering)"
10k B,RV3,Pot_Alpha_9mm_Vertical,,POT-R09V-10K B (9 mm vertical) - THT (wave soldering) - laisser JLC choisir (Basic de preference)
100k Bourns 3314J-1-104E,RV4,Trim_SMD_Bourns_3314J,,Bourns 3314J-1-104E (CARRIER NULL : Y passe sans X) - SMT bottom - laisser JLC choisir (Basic de preference)
100k Bourns 3314J-1-104E,RV5,Trim_SMD_Bourns_3314J,,Bourns 3314J-1-104E (SIGNAL NULL : X passe sans Y) - SMT bottom - laisser JLC choisir (Basic de preference)
MC1496DR2G,U2,SOIC-14_3.9x8.7mm_P1.27mm,,"MC1496DR2G (onsemi, SOIC-14) - SMT bottom - laisser JLC choisir (Basic de preference)"
TL074CDR,U3,SOIC-14_3.9x8.7mm_P1.27mm,C12594,TL074CDR - SMT bottom
